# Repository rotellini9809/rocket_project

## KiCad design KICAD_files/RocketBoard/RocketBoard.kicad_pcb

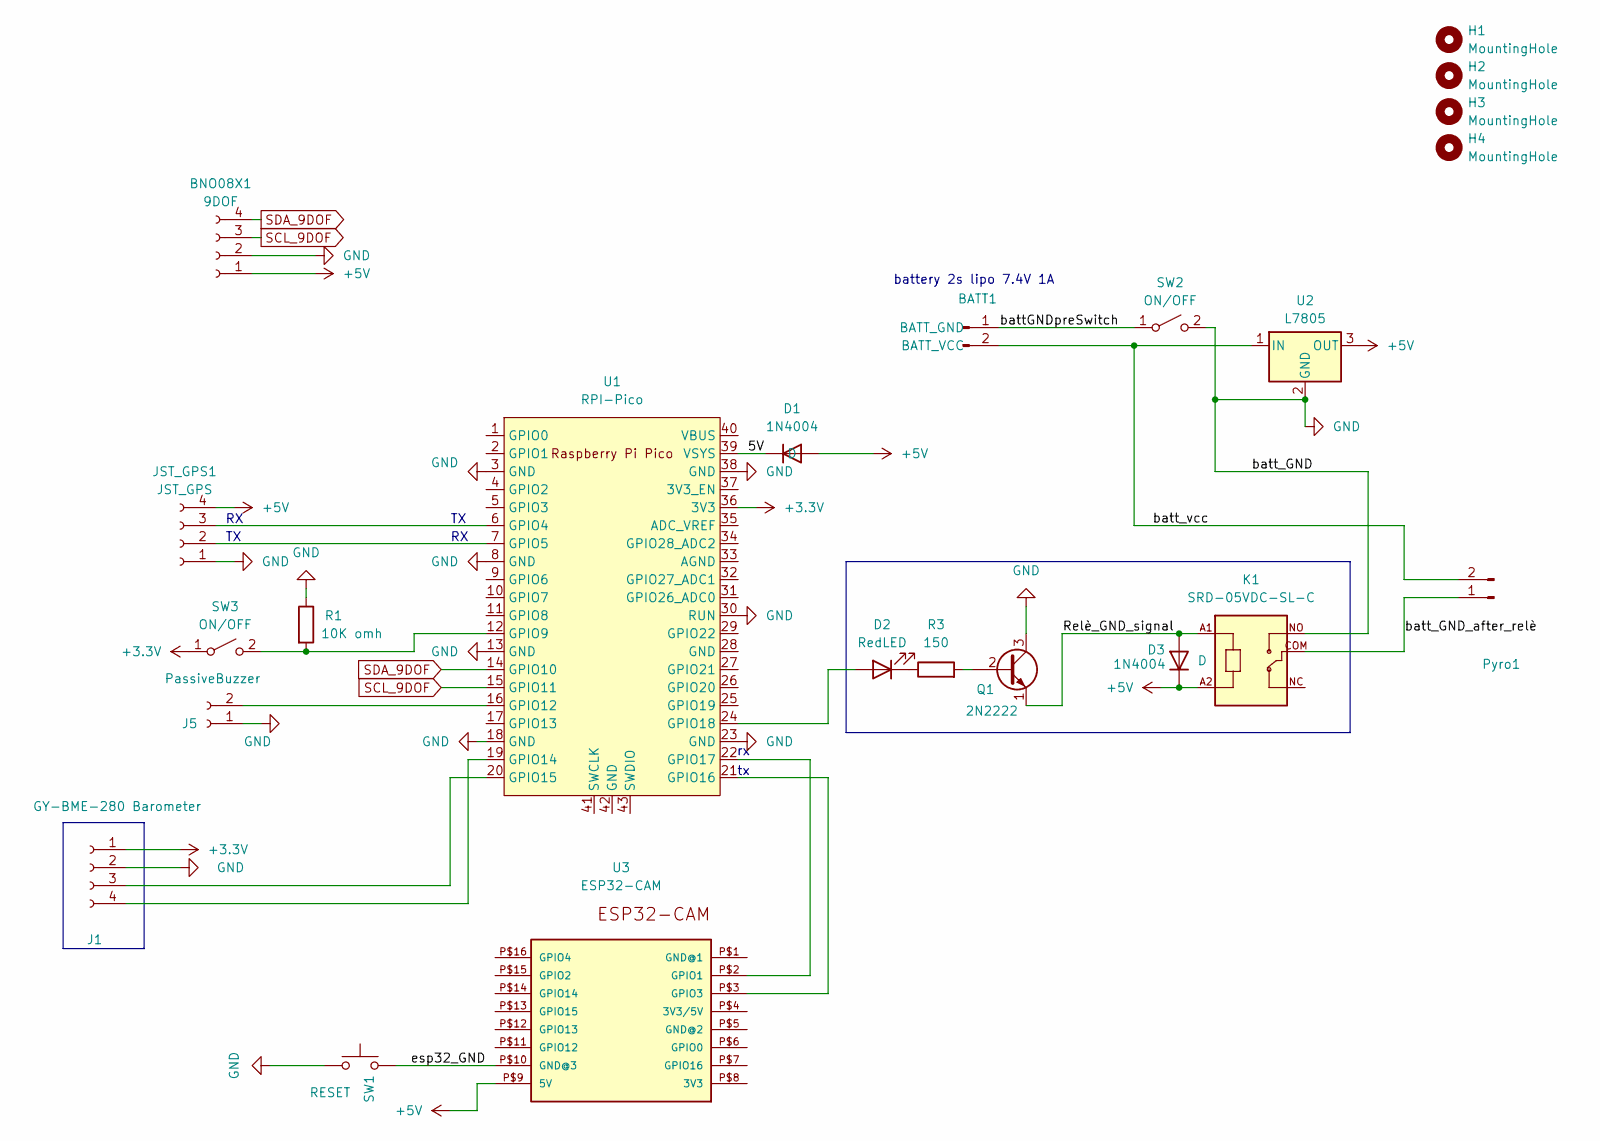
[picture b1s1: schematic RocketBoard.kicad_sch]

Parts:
BATT1: PinSocket_1x02_P2.54mm_Vertical
BNO08X1: 9DOF; PinSocket_1x04_P2.54mm_Vertical
D1, D3: 1N4004; D_A-405_P7.62mm_Horizontal
D2: RedLED; LED_D3.0mm
H1, H2, H3, H4: MountingHole; MountingHole_2.1mm
J1: GY-BME-280 Barometer; PinHeader_1x04_P2.54mm_Vertical
J5: PassiveBuzzer; myBuzzer
JST_GPS1: JST_GPS; JST_EH_S4B-EH_1x04_P2.50mm_Horizontal
K1: SRD-05VDC-SL-C; ssr-41FDA
Pyro1: TerminalBlock_bornier-2_P5.08mm
Q1: 2N2222; TO-92
R1: 10K omh; R_Axial_DIN0204_L3.6mm_D1.6mm_P5.08mm_Horizontal
R3: 150; R_Axial_DIN0207_L6.3mm_D2.5mm_P10.16mm_Horizontal
SW1: RESET; SW_DIP_SPSTx01_Slide_6.7x4.1mm_W8.61mm_P2.54mm_LowProfile
SW2, SW3: ON/OFF; Schiebeschalter SS-12D00
U1: RPI-Pico; RPi_Pico_SMD_TH
U2: L7805; TO-220-3_Horizontal_TabDown
U3: ESP32-CAM

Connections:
+3.3V: J1.1, SW3.1 (A), U1.36 (3V3)
+5V: BNO08X1.1, D1.2 (A), D3.1 (K), JST_GPS1.4, K1.A2, U2.3 (OUT), U3.P$9 (5V)
/5V: D1.1 (K), U1.39 (VSYS)
/Relè_GND_signal: D3.2 (A), K1.A1, Q1.1 (E)
/battGNDpreSwitch: BATT1.1 (BATT_GND), SW2.1 (A)
/batt_GND_after_relè: K1.COM, Pyro1.1
/batt_vcc: BATT1.2 (BATT_VCC), Pyro1.2, U2.1 (IN)
/esp32_GND: SW1.2, U3.P$10 (GND@3)
GND: BNO08X1.2, J1.2, J5.1, JST_GPS1.1, K1.NO, Q1.3 (C), R1.1, SW1.1, SW2.2 (B), U1.3 (GND), U1.8 (GND), U1.13 (GND), U1.18 (GND), U1.23 (GND), U1.30 (RUN), U1.38 (GND), U2.2 (GND)
unnamed: D2.2 (A), U1.24 (GPIO18)
unnamed: D2.1 (K), R3.1
unnamed: J1.3, U1.20 (GPIO15)
unnamed: J1.4, U1.19 (GPIO14)
unnamed: J5.2, U1.16 (GPIO12)
unnamed: JST_GPS1.2, U1.7 (GPIO5)
unnamed: JST_GPS1.3, U1.6 (GPIO4)
unnamed: Q1.2 (B), R3.2
unnamed: R1.2, SW3.2 (B), U1.12 (GPIO9)
unnamed: U1.21 (GPIO16), U3.P$3 (GPIO3)
unnamed: U1.22 (GPIO17), U3.P$2 (GPIO1)
SCL_9DOF: BNO08X1.3, U1.15 (GPIO11)
SDA_9DOF: BNO08X1.4, U1.14 (GPIO10)

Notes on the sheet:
battery 2s lipo 7.4V 1A

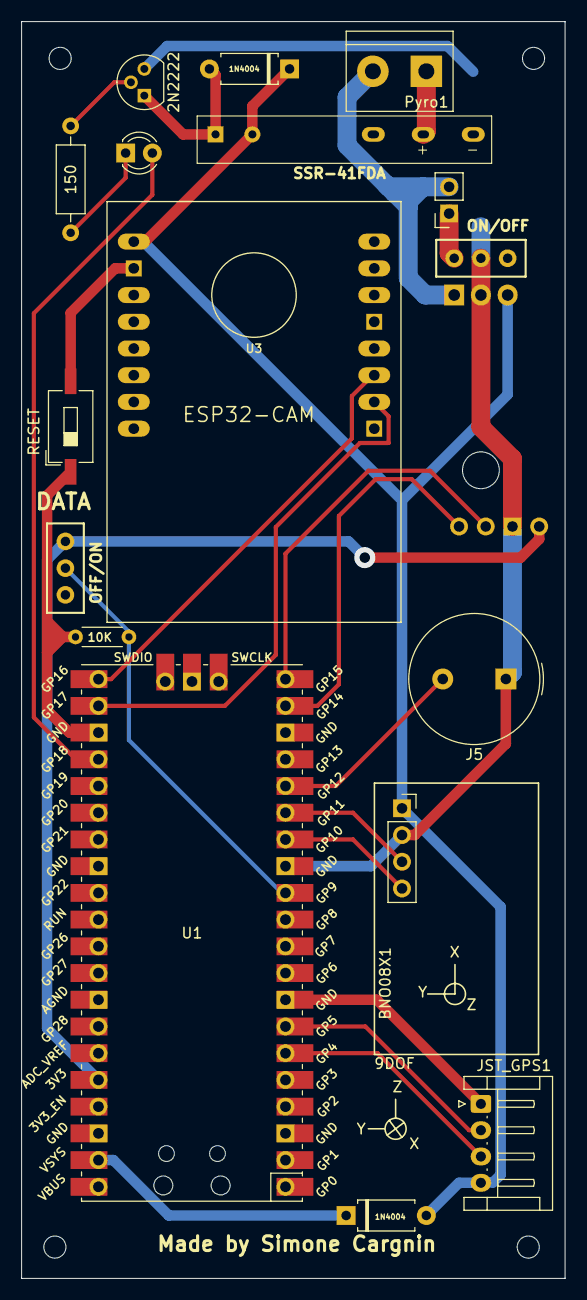
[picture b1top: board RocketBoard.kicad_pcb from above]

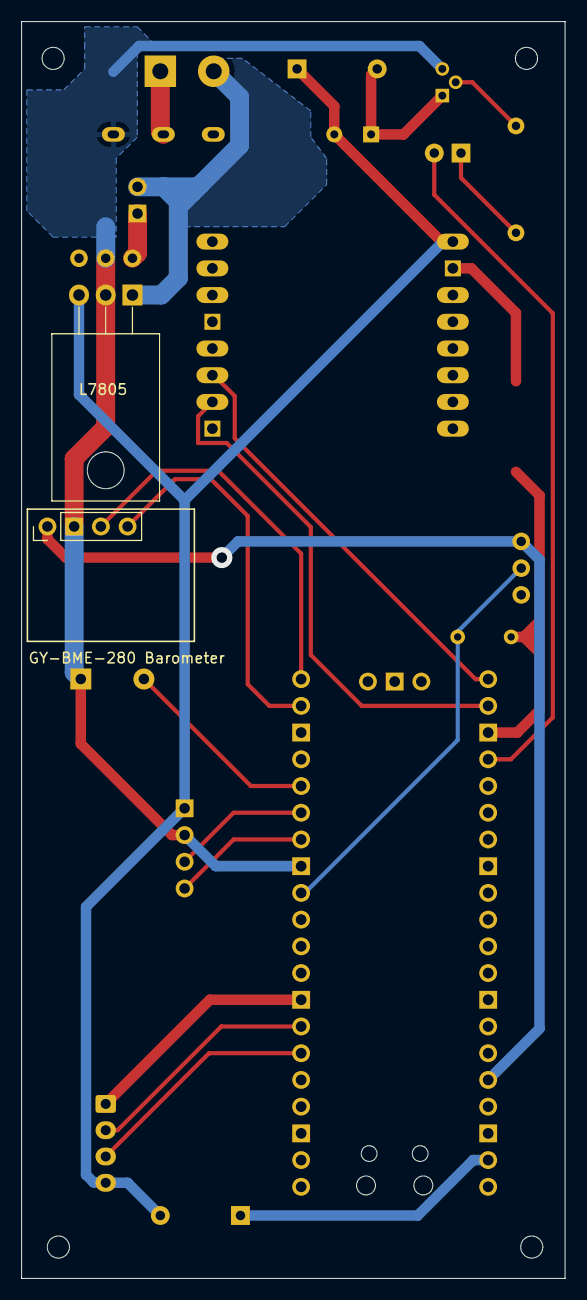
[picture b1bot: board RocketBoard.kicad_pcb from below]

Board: 2 copper layers, 51.7 x 119.5 mm, 23 parts (2 on the bottom side), 22 nets.

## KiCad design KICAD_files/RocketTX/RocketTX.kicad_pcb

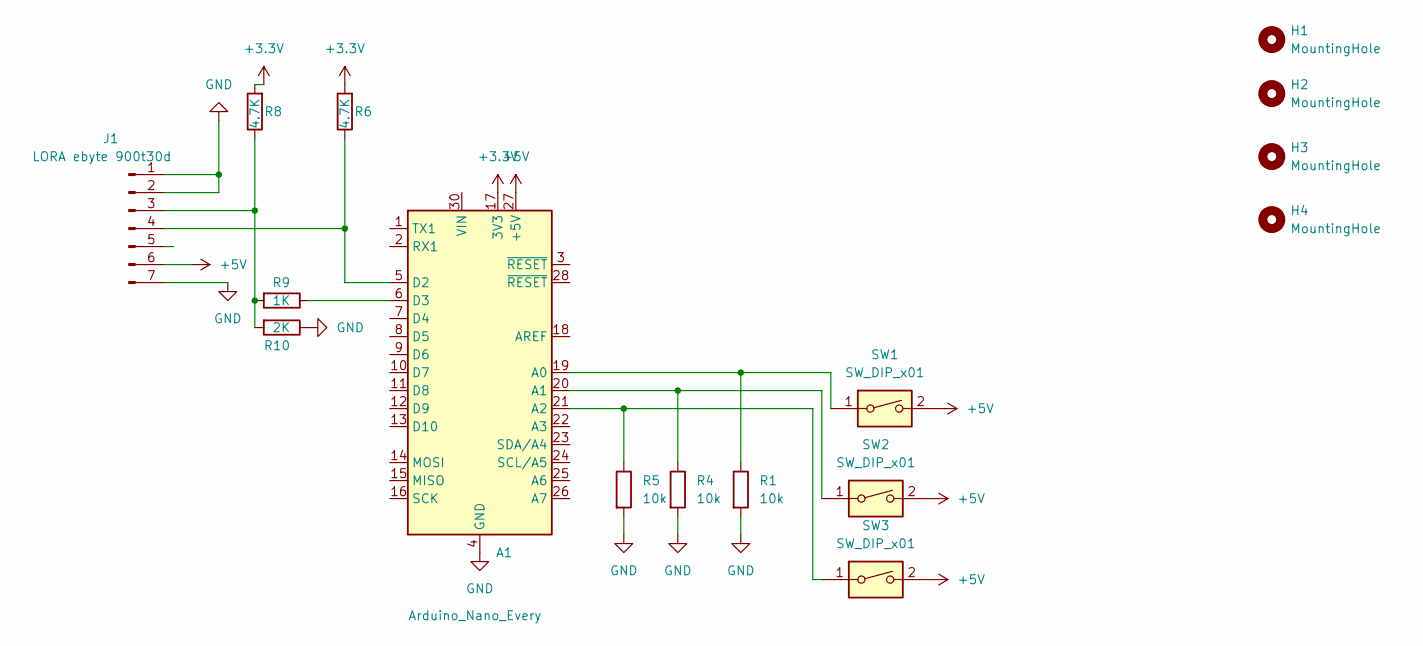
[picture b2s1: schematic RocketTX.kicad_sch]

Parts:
A1: Arduino_Nano_Every; Arduino_Nano
H1, H2, H3, H4: MountingHole; MountingHole_2.5mm
J1: LORA ebyte 900t30d; PinSocket_1x07_P2.54mm_Vertical
R1, R4, R5: 10k; R_Axial_DIN0207_L6.3mm_D2.5mm_P10.16mm_Horizontal
R6, R8: 4.7K; R_Axial_DIN0207_L6.3mm_D2.5mm_P10.16mm_Horizontal
R9: 1K; R_Axial_DIN0207_L6.3mm_D2.5mm_P10.16mm_Horizontal
R10: 2K; R_Axial_DIN0207_L6.3mm_D2.5mm_P10.16mm_Horizontal
SW1, SW2, SW3: SW_DIP_x01; PinSocket_1x02_P2.54mm_Vertical

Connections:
+3.3V: A1.17 (3V3), R6.2, R8.2
+5V: A1.27 (+5V), J1.6, SW1.2, SW2.2, SW3.2
GND: A1.4 (GND), A1.29 (GND), J1.1, J1.2, J1.7, R1.2, R4.2, R5.2, R10.1
unnamed: A1.19 (A0), R1.1, SW1.1
unnamed: A1.20 (A1), R4.1, SW2.1
unnamed: A1.21 (A2), R5.1, SW3.1
unnamed: A1.5 (D2), J1.4, R6.1
unnamed: A1.6 (D3), R9.1
unnamed: J1.3, R8.1, R9.2, R10.2

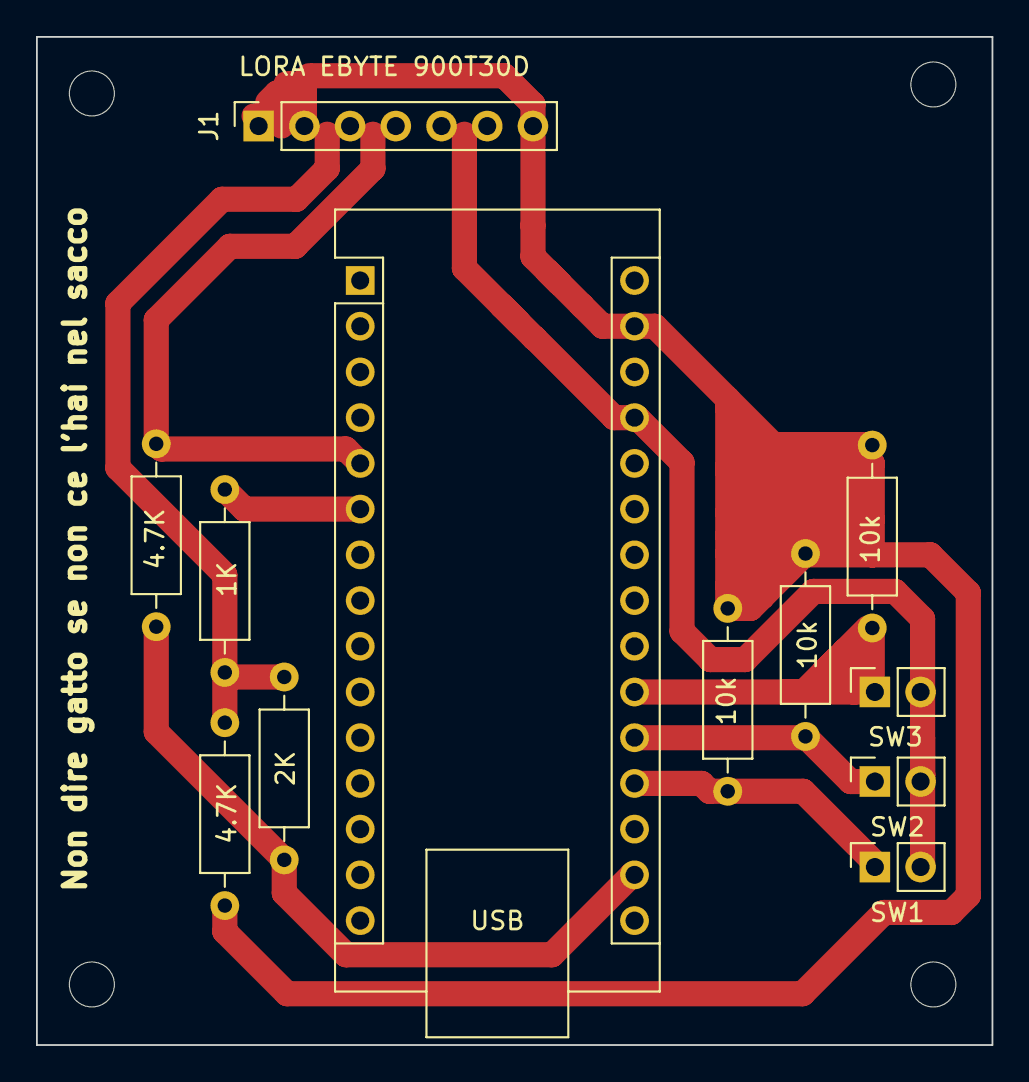
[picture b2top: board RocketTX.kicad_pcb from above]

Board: 2 copper layers, 53.1 x 56.0 mm, 16 parts (0 on the bottom side), 9 nets.

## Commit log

2024-03-08 fraaaaaatm
2024-03-31 bella
2024-04-16 kikad works
2024-05-26 bros
2024-07-14 r3frffre
2024-10-27 hhbh
